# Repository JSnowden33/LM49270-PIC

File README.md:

# LM49270-PIC
This is a program allowing for digital or analog volume control on the LM49270 headphone/speaker amplifier using a PIC16F1503 microcontroller.
It is in the form of an MPLAB X project and can be compiled using MPLAB X IDE with XC8. You can also use the pre-compiled program found at
Software/LM49270-PIC.X/dist/default/production/LM49270-PIC.X.production.hex with MPLAB IPE. The board can be programmed using a PICkit 3.

The program allows for 32 steps of volume. Speaker volume is allowed the full range from 0 to 31. Headphone volume is restricted from 0 to 21. This can be changed by modifying HP_OFFSET in Config.h.

The operating mode is selected by soldering a jumper located behind the headphone jack on the PCB. When soldered to GND, it operates in digital mode and volume is controlled with two tact switches connected between UP/DN and GND. When the jumper is soldered to V+, it operates in analog mode and volume is controlled with a potentiometer soldered to V+, VOL, and GND.

The PCB for this circuit can be ordered here: https://oshpark.com/shared_projects/Wy4lnqzu  
The circuit requires 3.3V to 5V input. It uses a headphone jack with a NC switch. Speaker output is automatically toggled off by hardware when headphones are detected. The amp works best with speakers between 0.7W and 1.2W.

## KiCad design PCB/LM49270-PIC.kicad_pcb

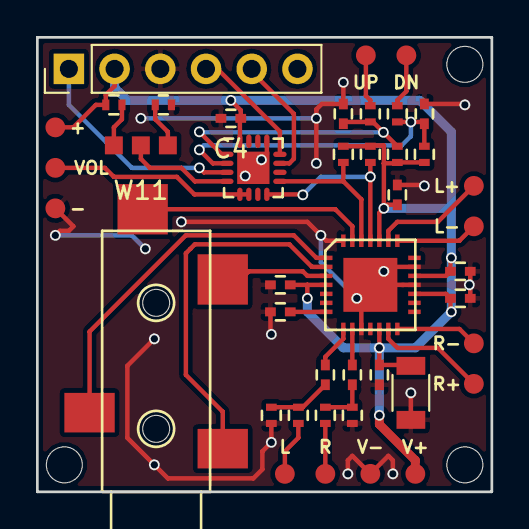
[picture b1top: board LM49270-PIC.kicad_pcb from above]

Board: 2 copper layers, 25.2 x 25.2 mm, 47 parts (0 on the bottom side), 30 nets.

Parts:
C1, C2, C3, C4, C5, C6, C7, C8, C9, C11, C12: C; C_0402
C10: CP; C_1206
J1: JACK_TRS_4PINS; SJ-3524-SMT-TR
J2: CONN_01X06; Pin_Header_Straight_1x06_Pitch2.54mm
R1, R2, R3, R4, R5, R6, R7, R8, R9, R10, R11, R12: R; R_0402
Screw: Screw
Screw#2, Screw#3: Screw
U1: PIC16F1503; QFN-16-1EP_3x3mm_Pitch0.5mm
U2: LM49270; QFN-28-LM49270
W1, W2, W3, W4, W5, W6, W7, W8, W9, W10, W11, W12, W13, W14, W15, W16: TEST_1P; Pad

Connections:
GND: C1.1, C4.2, C5.2, C6.2, C7.1, C8.1, C9.2, C10.2, C11.1, C12.1, J2.3, R1.2, R5.2, R12.2, U1.13, U1.17, U2.10, U2.18, U2.20, U2.28, U2.29, W5.1, W16.1
unnamed: C1.2, R6.1, R10.1, U1.1
unnamed: C2.1, U2.8
unnamed: C2.2, R1.1, R3.1
unnamed: C3.1, U2.9
unnamed: C3.2, R4.1, R5.1
unnamed: C6.1, U2.7
unnamed: C7.2, R2.2, R11.2, U1.2
unnamed: J1.1, U2.2
unnamed: J1.2, U2.3
unnamed: J1.3, U2.1
unnamed: J1.4, U2.27
unnamed: J2.1, U1.3
unnamed: J2.4, U1.12
unnamed: J2.5, U1.11
unnamed: R2.1, W6.1
unnamed: R3.2, W2.1
unnamed: R4.2, W3.1
unnamed: R6.2, W1.1
unnamed: R7.1, U1.8, U2.25
unnamed: R8.1, U1.9, U2.26
unnamed: R9.2, W15.1
unnamed: R12.1, W13.1
unnamed: U1.4, W11.1
unnamed: U1.5, U1.6, W12.1
unnamed: U2.13, W10.1
unnamed: U2.14, W9.1
unnamed: U2.22, W8.1
unnamed: U2.23, W7.1
VDD: C4.1, C5.1, C8.2, C9.1, C10.1, C11.2, C12.2, J2.2, R7.2, R8.2, R9.1, R10.2, R11.1, U1.16, U2.4, U2.12, U2.17, U2.19, U2.24, W4.1, W14.1
